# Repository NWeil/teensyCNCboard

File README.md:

# Teensy CNC Board
Improve danger sparkle production

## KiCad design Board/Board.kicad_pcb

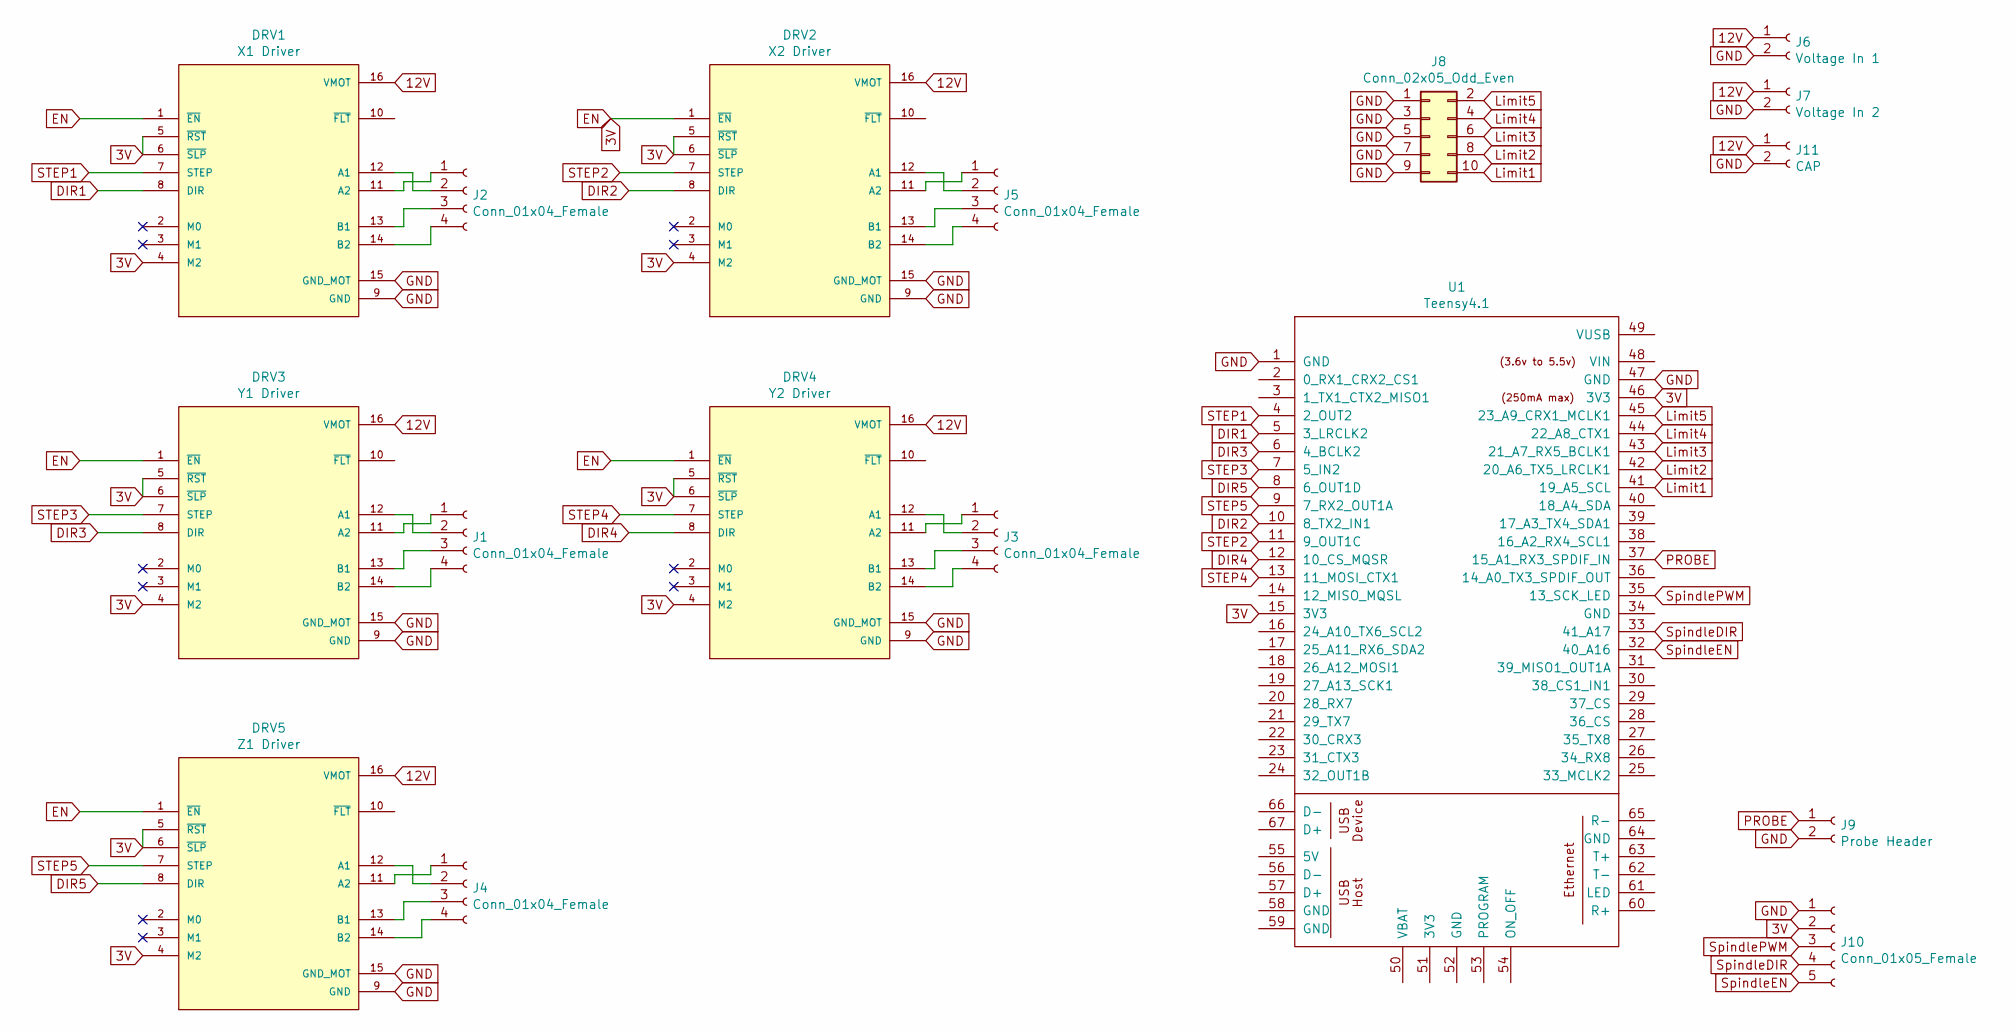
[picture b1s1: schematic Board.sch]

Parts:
DRV1: X1 Driver; IC_DRV8825_STEPPER_MOTOR_DRIVER_CARRIER
DRV2: X2 Driver; IC_DRV8825_STEPPER_MOTOR_DRIVER_CARRIER
DRV3: Y1 Driver; IC_DRV8825_STEPPER_MOTOR_DRIVER_CARRIER
DRV4: Y2 Driver; IC_DRV8825_STEPPER_MOTOR_DRIVER_CARRIER
DRV5: Z1 Driver; IC_DRV8825_STEPPER_MOTOR_DRIVER_CARRIER
J1, J2, J3, J4, J5: Conn_01x04_Female; PinHeader_1x04_P2.54mm_Vertical
J6: Voltage In 1; AMASS_XT60-M
J7: Voltage In 2; PinHeader_1x02_P2.54mm_Vertical
J8: Conn_02x05_Odd_Even; PinHeader_2x05_P2.54mm_Vertical
J9: Probe Header; PinHeader_1x02_P2.54mm_Vertical
J10: Conn_01x05_Female; PinHeader_1x05_P2.54mm_Vertical
J11: CAP; PinHeader_1x02_P2.54mm_Vertical
U1: Teensy4.1; Teensy41

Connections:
3V: DRV1.1 (~EN), DRV1.4 (M2), DRV1.5 (~RST), DRV1.6 (~SLP), DRV2.1 (~EN), DRV2.4 (M2), DRV2.5 (~RST), DRV2.6 (~SLP), DRV3.1 (~EN), DRV3.4 (M2), DRV3.5 (~RST), DRV3.6 (~SLP), DRV4.1 (~EN), DRV4.4 (M2), DRV4.5 (~RST), DRV4.6 (~SLP), DRV5.1 (~EN), DRV5.4 (M2), DRV5.5 (~RST), DRV5.6 (~SLP), J10.2, U1.15 (3V3), U1.46 (3V3)
12V: DRV1.16 (VMOT), DRV2.16 (VMOT), DRV3.16 (VMOT), DRV4.16 (VMOT), DRV5.16 (VMOT), J6.1, J7.1, J11.1
DIR1: DRV1.8 (DIR), U1.5 (3_LRCLK2)
DIR2: DRV2.8 (DIR), U1.10 (8_TX2_IN1)
DIR3: DRV3.8 (DIR), U1.6 (4_BCLK2)
DIR4: DRV4.8 (DIR), U1.12 (10_CS_MQSR)
DIR5: DRV5.8 (DIR), U1.8 (6_OUT1D)
GND: DRV1.9 (GND), DRV1.15 (GND_MOT), DRV2.9 (GND), DRV2.15 (GND_MOT), DRV3.9 (GND), DRV3.15 (GND_MOT), DRV4.9 (GND), DRV4.15 (GND_MOT), DRV5.9 (GND), DRV5.15 (GND_MOT), J6.2, J7.2, J8.1, J8.3, J8.5, J8.7, J8.9, J9.2, J10.1, J11.2, U1.1 (GND), U1.47 (GND)
Limit1: J8.10, U1.41 (19_A5_SCL)
Limit2: J8.8, U1.42 (20_A6_TX5_LRCLK1)
Limit3: J8.6, U1.43 (21_A7_RX5_BCLK1)
Limit4: J8.4, U1.44 (22_A8_CTX1)
Limit5: J8.2, U1.45 (23_A9_CRX1_MCLK1)
unnamed: DRV1.11 (A2), J2.1
unnamed: DRV1.12 (A1), J2.2
unnamed: DRV1.13 (B1), J2.3
unnamed: DRV1.14 (B2), J2.4
unnamed: DRV2.11 (A2), J5.1
unnamed: DRV2.12 (A1), J5.2
unnamed: DRV2.13 (B1), J5.3
unnamed: DRV2.14 (B2), J5.4
unnamed: DRV3.11 (A2), J1.1
unnamed: DRV3.12 (A1), J1.2
unnamed: DRV3.13 (B1), J1.3
unnamed: DRV3.14 (B2), J1.4
unnamed: DRV4.11 (A2), J3.1
unnamed: DRV4.12 (A1), J3.2
unnamed: DRV4.13 (B1), J3.3
unnamed: DRV4.14 (B2), J3.4
unnamed: DRV5.11 (A2), J4.1
unnamed: DRV5.12 (A1), J4.2
unnamed: DRV5.13 (B1), J4.3
unnamed: DRV5.14 (B2), J4.4
PROBE: J9.1, U1.37 (15_A1_RX3_SPDIF_IN)
STEP1: DRV1.7 (STEP), U1.4 (2_OUT2)
STEP2: DRV2.7 (STEP), U1.11 (9_OUT1C)
STEP3: DRV3.7 (STEP), U1.7 (5_IN2)
STEP4: DRV4.7 (STEP), U1.13 (11_MOSI_CTX1)
STEP5: DRV5.7 (STEP), U1.9 (7_RX2_OUT1A)
SpindleDIR: J10.4, U1.33 (41_A17)
SpindleEN: J10.5, U1.32 (40_A16)
SpindlePWM: J10.3, U1.35 (13_SCK_LED)

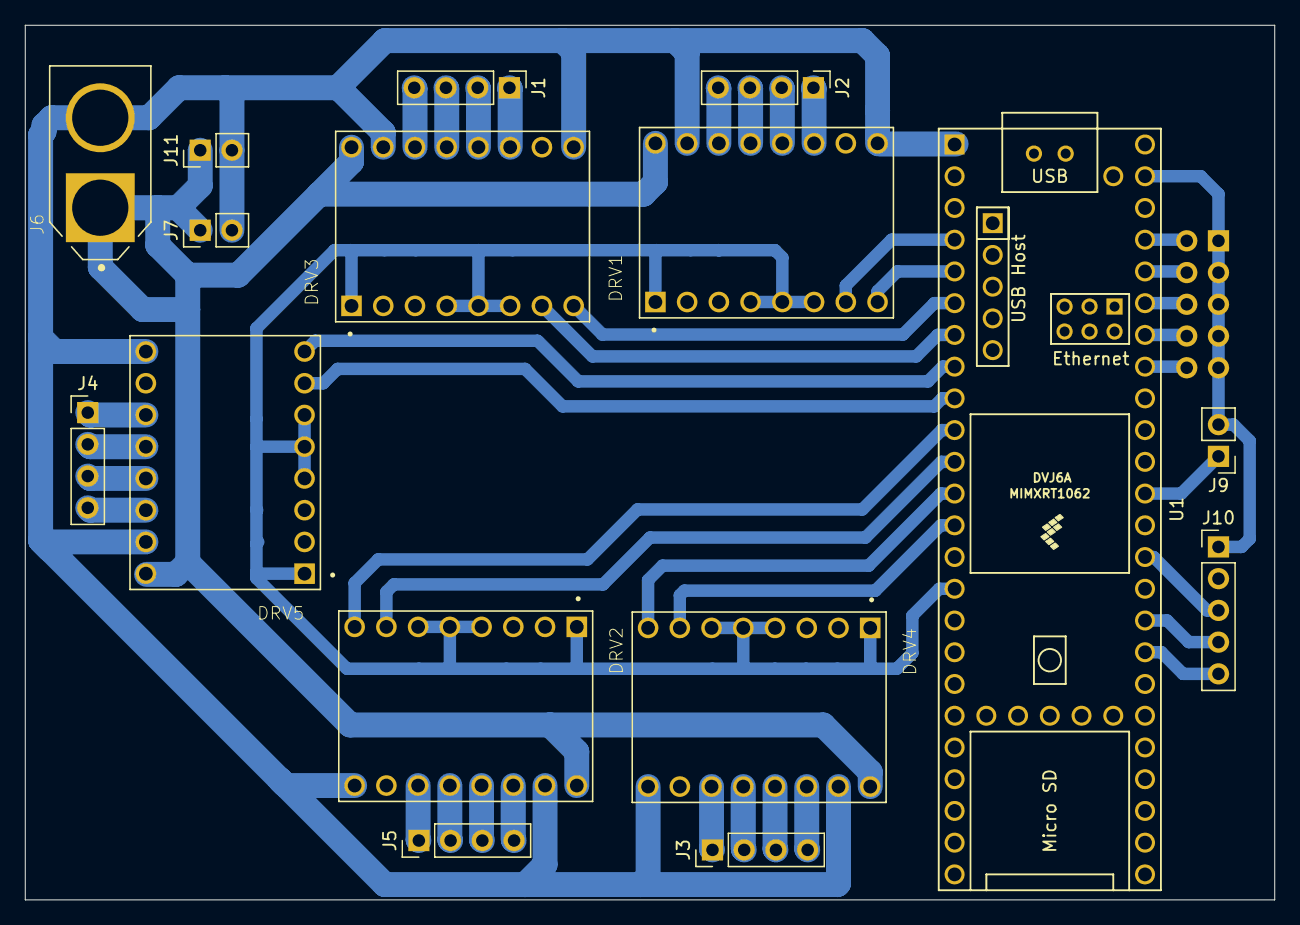
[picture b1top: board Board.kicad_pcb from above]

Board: 2 copper layers, 100.0 x 70.0 mm, 17 parts (1 on the bottom side), 42 nets.

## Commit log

2021-03-23 add files from pan-tilt board
2021-03-23 now its perfect
2021-03-23 now its even more perfect
2021-03-25 Add GRBLHAL and change pin mapping
2021-03-27 Plot back of board
2021-03-27 Add nc files
2021-03-27 Add spotting drill
